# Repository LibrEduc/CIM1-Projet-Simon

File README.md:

# CIM1-Projet-Simon
A "Simon says" project, CMS components, ATTtiny1634 microcontroller.

Un projet Simon, u "Jacques a dit", en composants CMS, ave un microcontrôleur ATTtiny1634.

## Objectif

Projet de (re)création d'un jeu du Simon MB (c), ou bien appelé "Simon says". Après avoir analysé le principe du jeu, le but est de tout refaire en électronique microprogrammée, le plus petit possible et de fabriquer un boîtier ajusté.

## Goal

Project to (re)create a game of the Simon MB (c), also called "Simon says". After having analysed the principle of the game, the goal is to remake everything in microprogrammed electronics, as small as possible, and to make a fitted box.

## Liste des pièces / Bill of Materials
- Condensateur C-EUC1206
- Support pile
- MicroContrôleur
- Connecteur ISP
- Led Neopixel
- Mosfet canal N
- Résistance
- Buzzer 5v 2,3kHz 50ma
- Bouton poussoir
- Interrupteur

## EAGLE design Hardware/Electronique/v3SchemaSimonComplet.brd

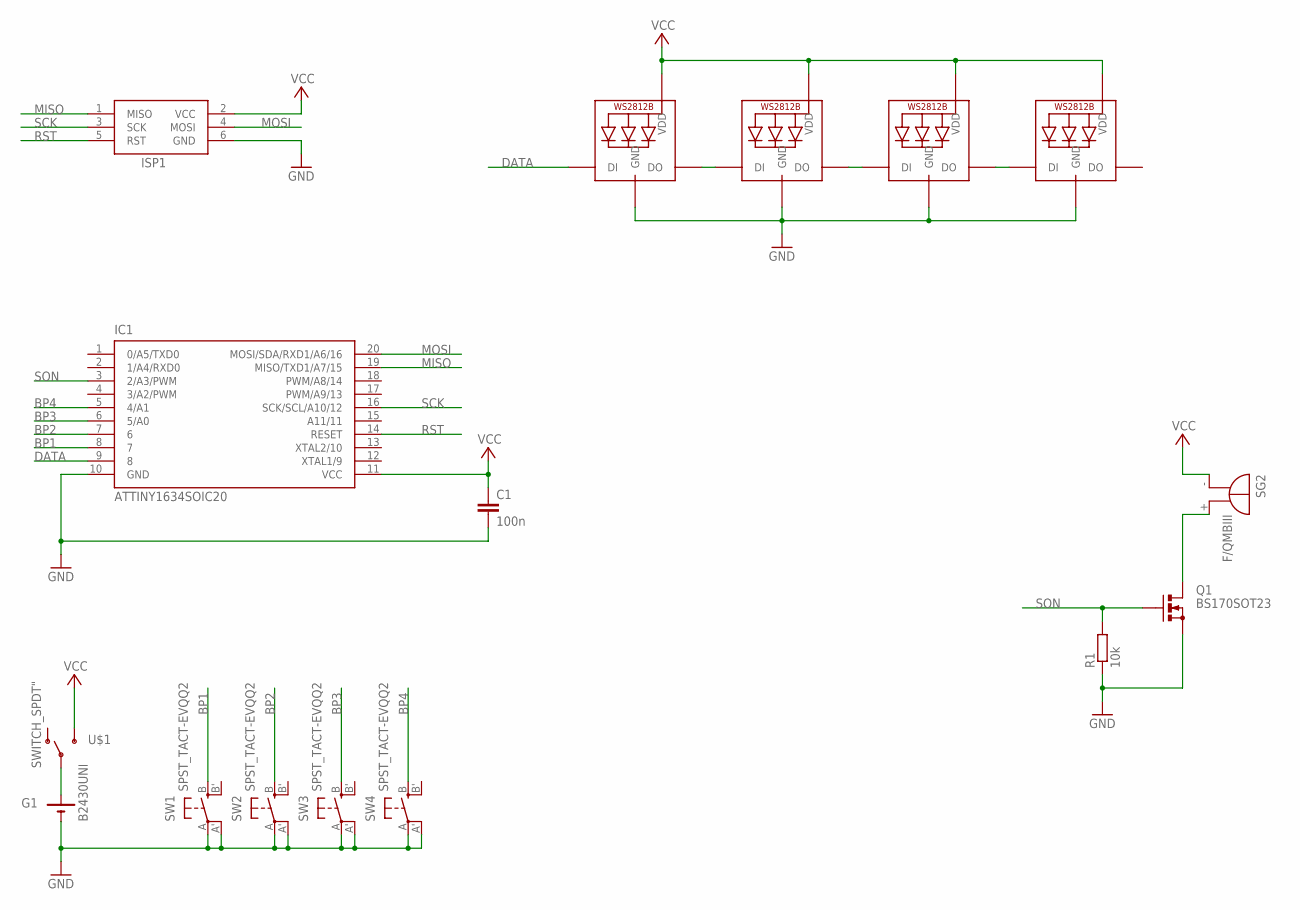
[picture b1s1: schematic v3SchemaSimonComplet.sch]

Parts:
C1: 100n; C1206
G1: B2430UNI
IC1: ATTINY1634SOIC20; SOIC20
ISP1: AVRISP-6; AVRISP
LED1, LED2, LED3, LED4: WS2812B5050; WS2812B
Q1: BS170SOT23; SOT23
R1: 10k; R1206
SG2: F/QMBIII
SW1, SW2, SW3, SW4: SPST_TACT-EVQQ2; EVQ-Q2
U$1: SWITCH_SPDT"; CMS-CL-SB-12A-02T

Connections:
BP1: IC1.8 (7), SW1.B (S)
BP2: IC1.7 (6), SW2.B (S)
BP3: IC1.6 (5/A0), SW3.B (S)
BP4: IC1.5 (4/A1), SW4.B (S)
DATA: IC1.9 (8), LED1.4-DIN (DI)
GND: C1.2, G1.-@1 (-), IC1.10 (GND), ISP1.6 (GND), LED1.3-GND (GND), LED2.3-GND (GND), LED3.3-GND (GND), LED4.3-GND (GND), Q1.2 (S), R1.1, SW1.A, SW1.A' (P1), SW2.A, SW2.A' (P1), SW3.A, SW3.A' (P1), SW4.A, SW4.A' (P1)
MISO: IC1.19 (MISO/TXD1/A7/15), ISP1.1 (MISO)
MOSI: IC1.20 (MOSI/SDA/RXD1/A6/16), ISP1.4 (MOSI)
unnamed: LED1.2-DOUT (DO), LED2.4-DIN (DI)
unnamed: LED2.2-DOUT (DO), LED3.4-DIN (DI)
unnamed: LED3.2-DOUT (DO), LED4.4-DIN (DI)
unnamed: G1.+@1 (+), U$1.2
unnamed: Q1.3 (D), SG2.+ (-)
RST: IC1.14 (RESET), ISP1.5 (RST)
SCK: IC1.16 (SCK/SCL/A10/12), ISP1.3 (SCK)
SON: IC1.3 (2/A3/PWM), Q1.1 (G), R1.2
VCC: C1.1, IC1.11 (VCC), ISP1.2 (VCC), LED1.1-VDD (VDD), LED2.1-VDD (VDD), LED3.1-VDD (VDD), LED4.1-VDD (VDD), SG2.- (+), U$1.3 (S)

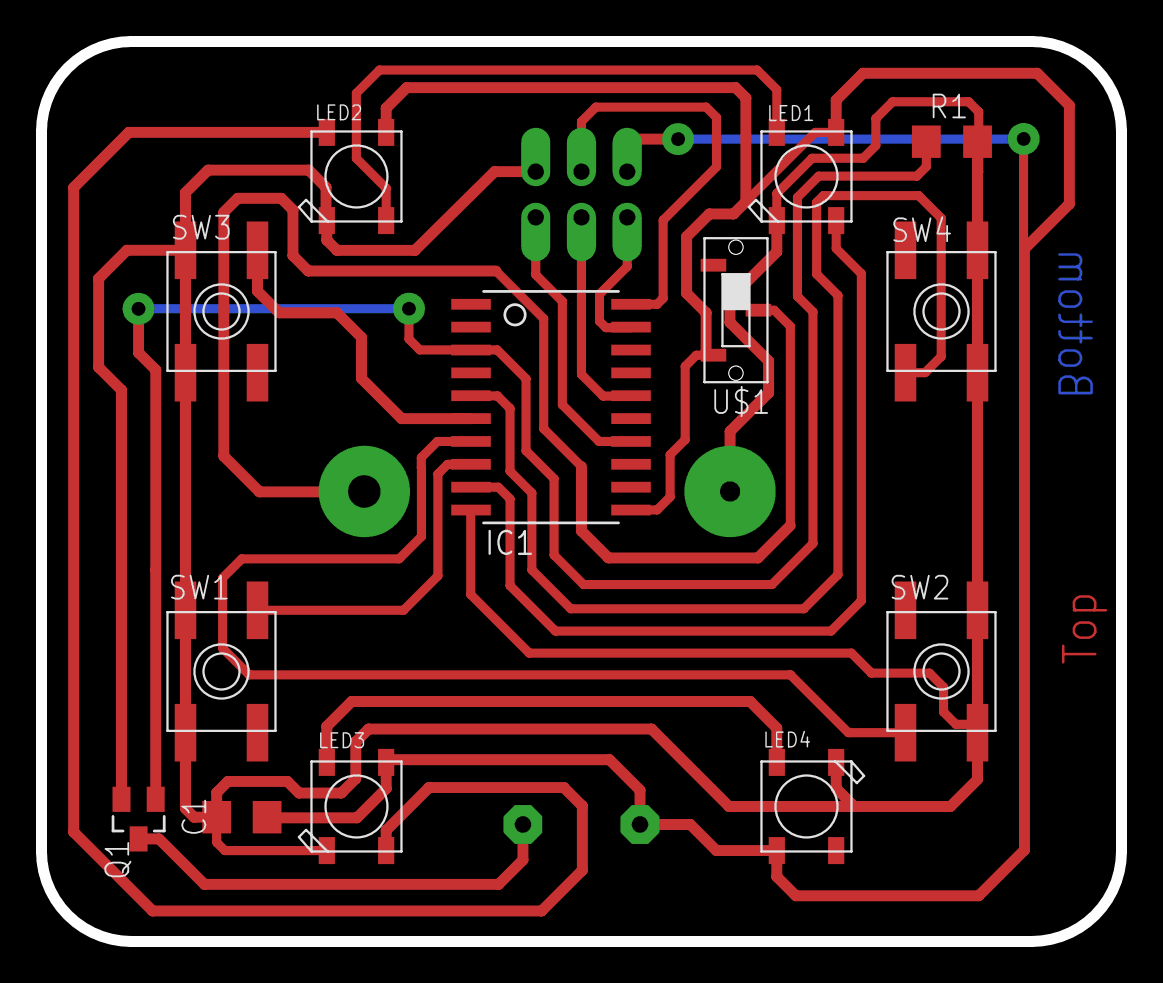
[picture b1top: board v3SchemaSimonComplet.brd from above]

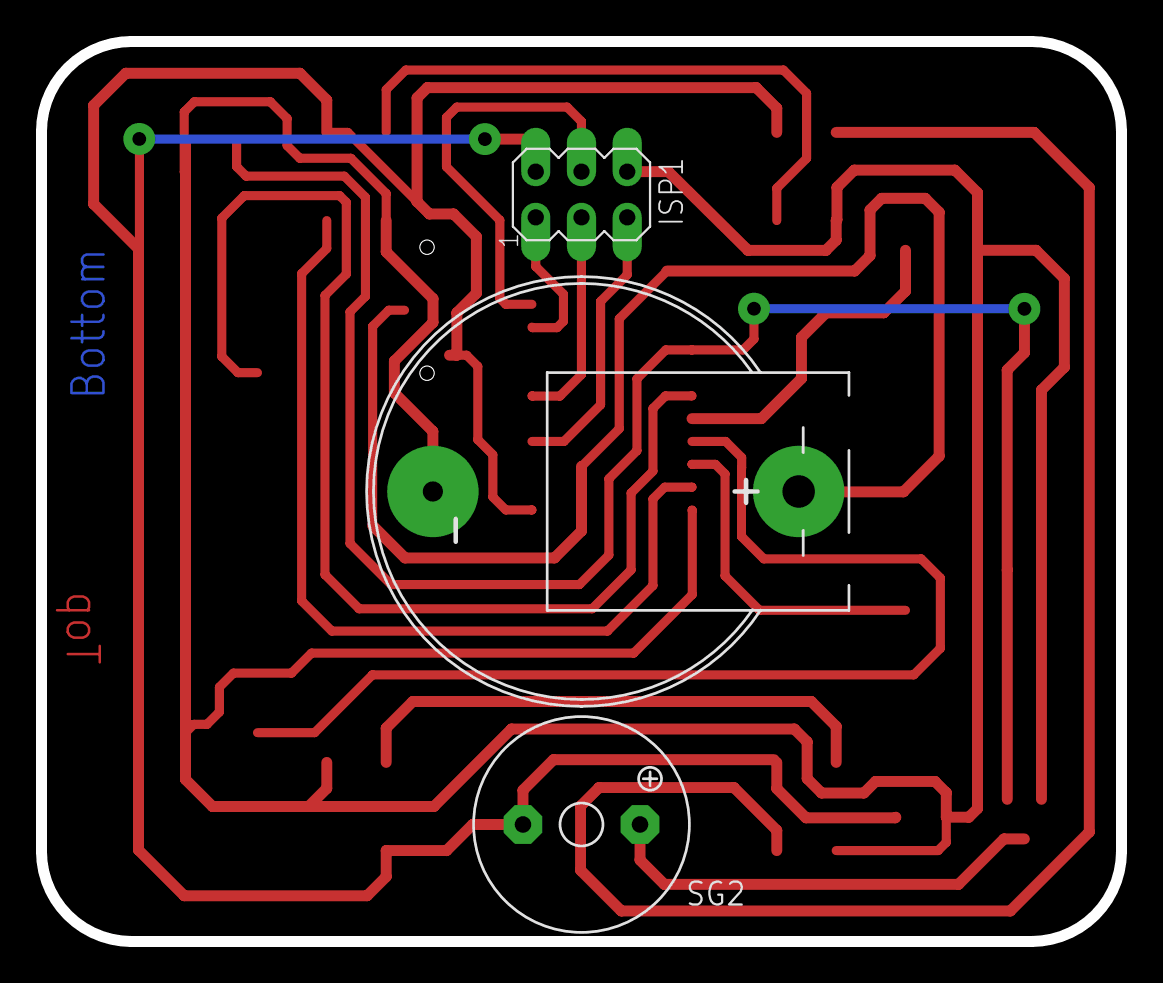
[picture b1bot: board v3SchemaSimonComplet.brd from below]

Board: 2 copper layers, 60.0 x 50.0 mm, 16 parts (3 on the bottom side), 17 nets.

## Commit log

2022-02-27 Commit Inital
2022-02-27 Ajout de photos
2022-04-02 Create LICENSE
